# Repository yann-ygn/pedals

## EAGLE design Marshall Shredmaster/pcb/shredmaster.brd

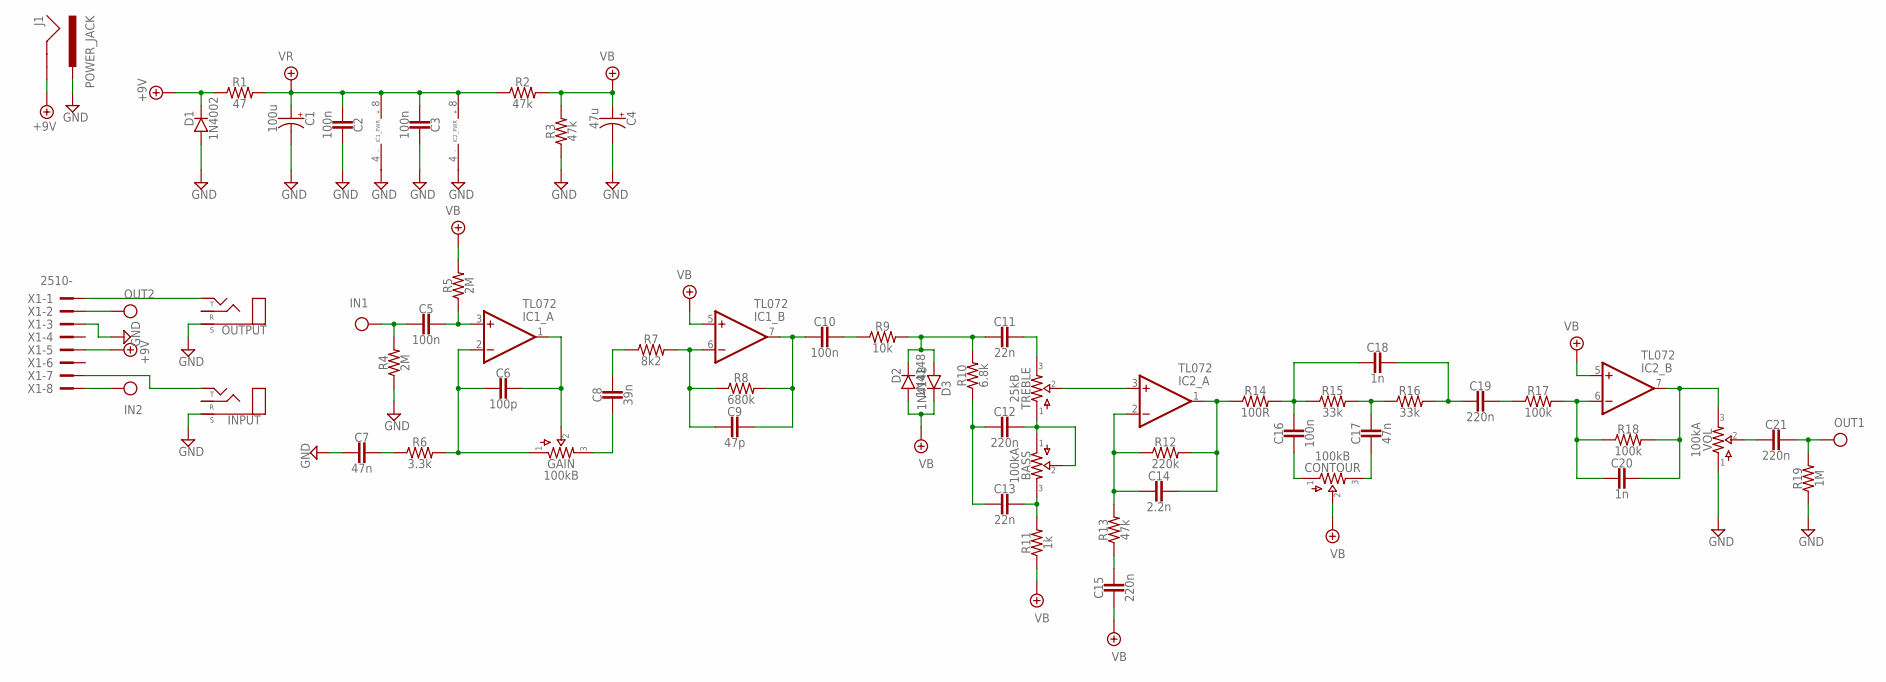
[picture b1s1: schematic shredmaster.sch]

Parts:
BASS: 100kA; 16MM
C1: 100u; 040_020
C2, C3: 100n; 050X030_025_2
C4: 47u; 040_020
C5, C10, C16: 100n; BOX_SMALL
C6: 100p; 050X030_025_2
C7, C17: 47n; BOX_SMALL
C8: 39n; BOX_SMALL
C9: 47p; 050X030_025_2
C11, C13: 22n; BOX_SMALL
C12, C15, C19, C21: 220n; BOX_SMALL
C14: 2.2n; BOX_SMALL
C18, C20: 1n; BOX_SMALL
CONTOUR: 100kB; 16MM
D1: 1N4002; DO41-2
D2, D3: 1N4148; DO35-2
GAIN: 100kB; 16MM
IC1, IC2: TL072; DIL08
INPUT: STEREONMJ; NMJ6HCD2
J1: POWER_JACK; POWER_JACK_PTH
OUTPUT: STEREONMJ; NMJ6HCD2
R1: 47; R0207/3
R2, R3, R13: 47k; R0207/3
R4, R5: 2M; R0207/3
R6: 3.3k; R0207/3
R7: 8k2; R0207/3
R8: 680k; R0207/3
R9: 10k; R0207/3
R10: 6.8k; R0207/3
R11: 1k; R0207/3
R12: 220k; R0207/3
R14: 100R; R0207/3
R15, R16: 33k; R0207/3
R17, R18: 100k; R0207/3
R19: 1M; R0207/3
TREBLE: 25kB; 16MM
VOL: 100kA; 16MM
X1: 2510-; PAK100/2500-10

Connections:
+9V: D1.C, J1.GND, R1.1, X1.5
GND: C1.-, C2.1, C3.1, C4.-, C7.2, D1.A, IC1.4 (V-), IC2.4 (V-), INPUT.S, J1.PWR, OUTPUT.S, R3.1, R4.1, R19.1, VOL.1, X1.3
IN: C5.2, R4.2, X1.8
unnamed: INPUT.T, X1.7
unnamed: C5.1, IC1.3 (+IN), R5.1
unnamed: C6.1, GAIN.2, IC1.1 (OUT)
unnamed: OUTPUT.T, X1.1
unnamed: C6.2, GAIN.1, IC1.2 (-IN), R6.2
unnamed: C7.1, R6.1
unnamed: C8.2, GAIN.3
unnamed: C8.1, R7.1
unnamed: C9.2, IC1.6 (-IN), R7.2, R8.1
unnamed: C9.1, C10.2, IC1.7 (OUT), R8.2
unnamed: C10.1, R9.1
unnamed: C11.2, D2.C, D3.A, R9.2, R10.2
unnamed: C11.1, TREBLE.3
unnamed: C12.2, C13.2, R10.1
unnamed: BASS.1, BASS.2, C12.1, TREBLE.1
unnamed: BASS.3, C13.1, R11.2
unnamed: C21.2, VOL.2
unnamed: C14.2, IC2.2 (-IN), R12.1, R13.2
unnamed: C14.1, IC2.1 (OUT), R12.2, R14.1
unnamed: IC2.3 (+IN), TREBLE.2
unnamed: C15.1, R13.1
unnamed: C16.2, CONTOUR.1
unnamed: C17.2, CONTOUR.3
unnamed: C16.1, C18.2, R14.2, R15.1
unnamed: C17.1, R15.2, R16.1
unnamed: C18.1, C19.2, R16.2
unnamed: C19.1, R17.1
unnamed: C20.2, IC2.6 (-IN), R17.2, R18.1
unnamed: C20.1, IC2.7 (OUT), R18.2, VOL.3
OUT: C21.1, R19.2, X1.2
VB: C4.+, C15.2, CONTOUR.2, D2.A, D3.C, IC1.5 (+IN), IC2.5 (+IN), R2.2, R3.2, R5.2, R11.1
VR: C1.+, C2.2, C3.2, IC1.8 (V+), IC2.8 (V+), R1.2, R2.1

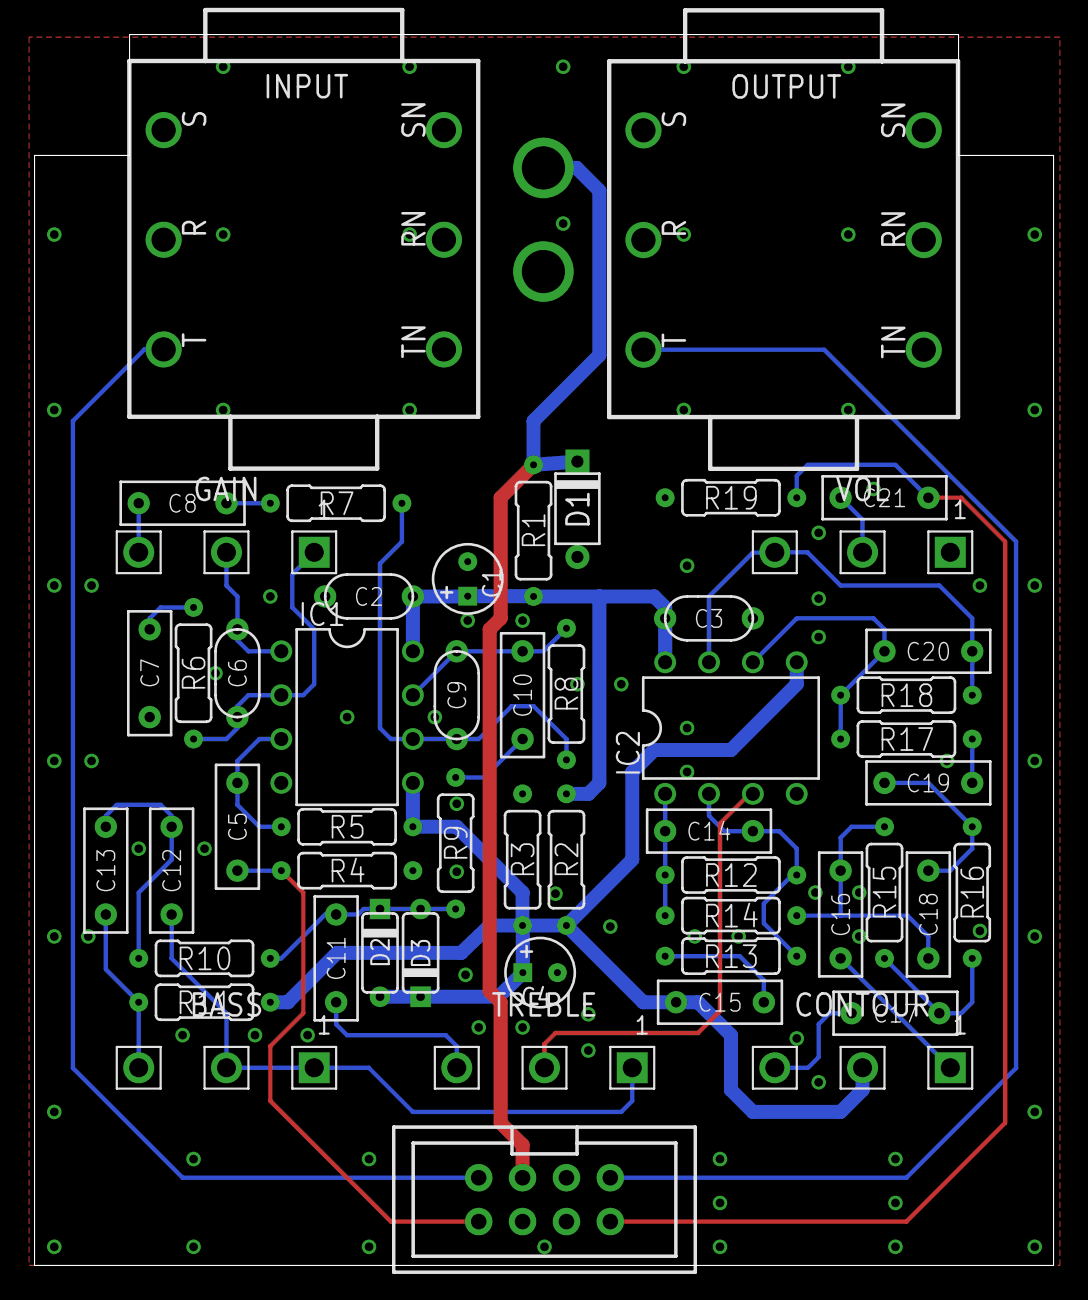
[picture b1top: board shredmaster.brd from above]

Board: 2 copper layers, 59.0 x 71.3 mm, 55 parts (1 on the bottom side), 35 nets.

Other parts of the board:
U$1: 125B_PCB

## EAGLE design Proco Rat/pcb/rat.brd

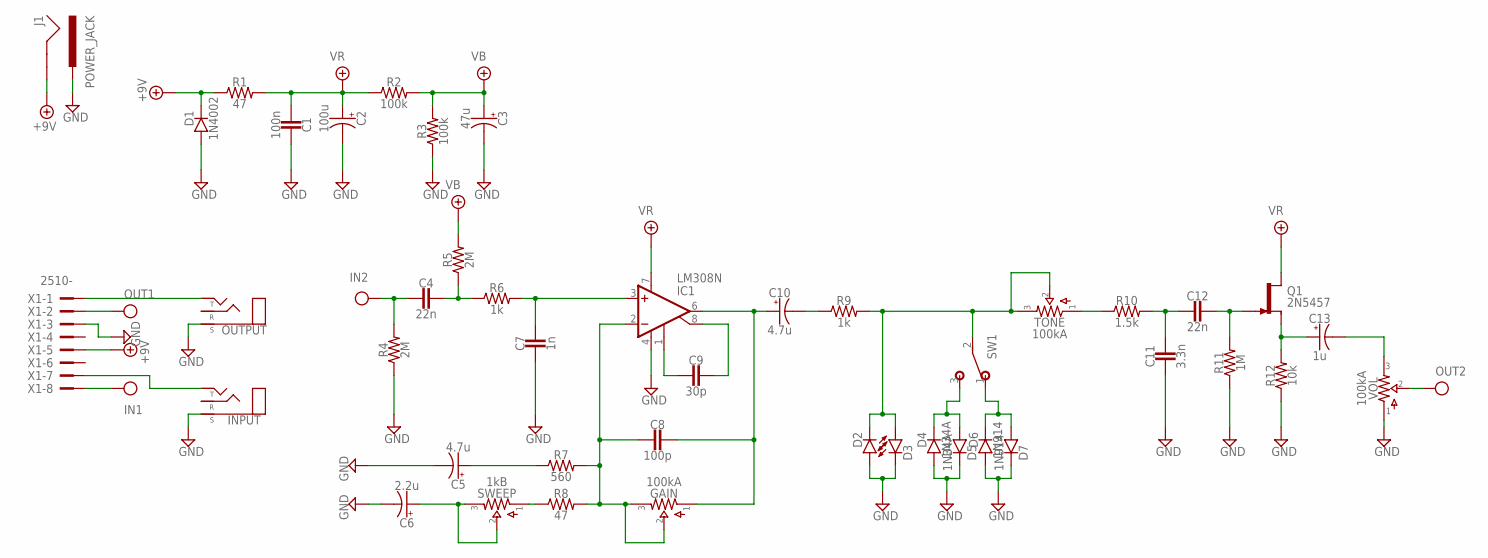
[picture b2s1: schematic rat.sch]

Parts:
C1: 100n; 050X030_025_2
C2: 100u; 040_020
C3: 47u; 040_020
C4, C12: 22n; BOX_SMALL
C5, C10: 4.7u; 050_020
C6: 2.2u; 050_020
C7: 1n; BOX_SMALL
C8: 100p; 050X030_025_2
C9: 30p; 050X030_025_2
C11: 3.3n; BOX_SMALL
C13: 1u; 050_020
D1: 1N4002; DO41-2
D2, D3: LED; 3MM_D
D4, D5: 1N34A; DO35-2
D6, D7: 1N914; DO35-2
GAIN: 100kA; 16MM
IC1: LM308N; DIL08
INPUT: STEREONMJ; NMJ6HCD2
J1: POWER_JACK; POWER_JACK_PTH
OUTPUT: STEREONMJ; NMJ6HCD2
Q1: 2N5457; TO92-
R1, R8: 47; R0207/3
R2, R3: 100k; R0207/3
R4, R5: 2M; R0207/3
R6, R9: 1k; R0207/3
R7: 560; R0207/3
R10: 1.5k; R0207/3
R11: 1M; R0207/3
R12: 10k; R0207/3
SW1: SPDT; M9040P
SWEEP: 1kB; 16MM
TONE: 100kA; 16MM
VOL: 100kA; 16MM
X1: 2510-; PAK100/2500-10

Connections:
+9V: D1.C, J1.GND, R1.1, X1.5
GND: C1.1, C2.-, C3.-, C5.-, C6.-, C7.2, C11.2, D1.A, D2.ANODE (A), D3.P$1 (C), D4.A, D5.C, D6.A, D7.C, IC1.4 (V-), INPUT.S, J1.PWR, OUTPUT.S, R3.1, R4.1, R11.1, R12.1, VOL.1, X1.3
IN: C4.2, R4.2, X1.8
unnamed: INPUT.T, X1.7
unnamed: C4.1, R5.1, R6.1
unnamed: C7.1, IC1.3 (+IN), R6.2
unnamed: OUTPUT.T, X1.1
unnamed: R8.1, SWEEP.1
unnamed: C9.2, IC1.1 (CMP1)
unnamed: C9.1, IC1.8 (CMP2)
unnamed: C8.1, C10.+, GAIN.1, IC1.6 (OUT)
unnamed: C5.+, R7.1
unnamed: C6.+, SWEEP.2, SWEEP.3
unnamed: C10.-, R9.1
unnamed: D2.P$1 (C), D3.ANODE (A), R9.2, SW1.2, TONE.2, TONE.3
unnamed: C8.2, GAIN.2, GAIN.3, IC1.2 (-IN), R7.2, R8.2
unnamed: R10.1, TONE.1
unnamed: C11.1, C12.2, R10.2
unnamed: C12.1, Q1.1 (G), R11.2
unnamed: C13.+, Q1.2 (S), R12.2
unnamed: C13.-, VOL.3
unnamed: D4.C, D5.A, SW1.3 (S)
unnamed: D6.C, D7.A, SW1.1 (O)
OUT: VOL.2, X1.2
VB: C3.+, R2.2, R3.2, R5.2
VR: C1.2, C2.+, IC1.7 (V+), Q1.3 (D), R1.2, R2.1

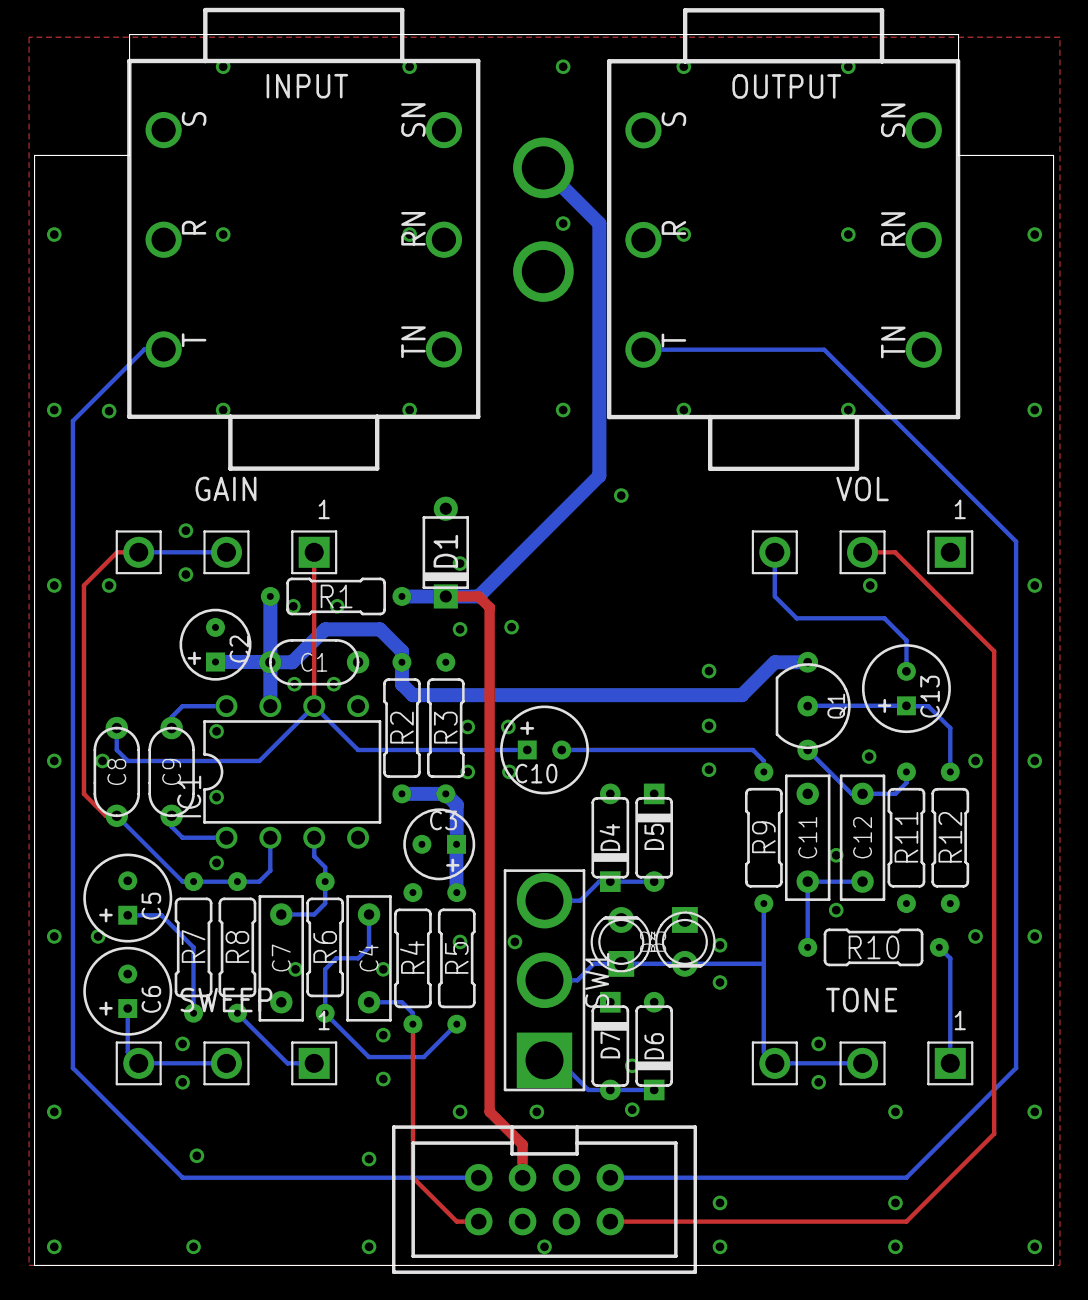
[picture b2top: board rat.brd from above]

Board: 2 copper layers, 59.0 x 71.3 mm, 44 parts (1 on the bottom side), 26 nets.

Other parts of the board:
U$1: 125B_PCB

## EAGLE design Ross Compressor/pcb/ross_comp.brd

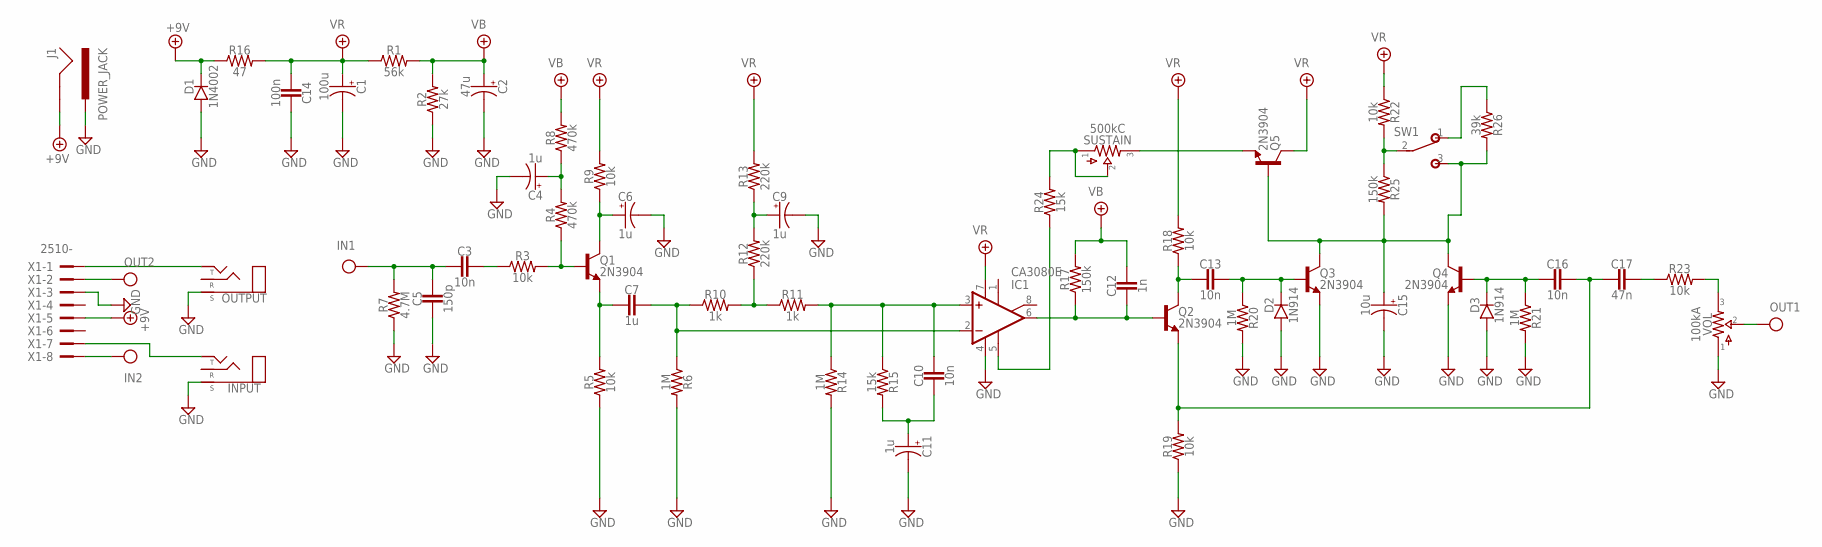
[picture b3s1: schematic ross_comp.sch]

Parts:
C1: 100u; 040_020
C2: 47u; 040_020
C3, C10, C13, C16: 10n; BOX_SMALL
C4, C6, C9, C11: 1u; 040_020
C5: 150p; 050X030_025_2
C7: 1u; BOX_BIG
C12: 1n; BOX_SMALL
C14: 100n; BOX_SMALL
C15: 10u; 040_020
C17: 47n; BOX_SMALL
D1: 1N4002; DO41-2
D2, D3: 1N914; DO35-2
IC1: CA3080E; DIL08
INPUT: STEREONMJ; NMJ6HCD2
J1: POWER_JACK; POWER_JACK_PTH
OUTPUT: STEREONMJ; NMJ6HCD2
Q1, Q2, Q3, Q4, Q5: 2N3904; TO92-
R1: 56k; R0207/3
R2: 27k; R0207/3
R3, R5, R9, R18, R19, R22, R23: 10k; R0207/3
R4, R8: 470k; R0207/3
R6, R14, R20, R21: 1M; R0207/3
R7: 4.7M; R0207/3
R10, R11: 1k; R0207/3
R12, R13: 220k; R0207/3
R15, R24: 15k; R0207/3
R16: 47; R0207/3
R17, R25: 150k; R0207/3
R26: 39k; R0207/3
SUSTAIN: 500kC; 16MM
SW1: SPDT; M9040P
VOL: 100kA; 16MM
X1: 2510-; PAK100/2500-10

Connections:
+9V: D1.C, J1.GND, R16.1, X1.5
GND: C1.-, C2.-, C4.-, C5.2, C6.-, C9.-, C11.-, C14.1, C15.-, D1.A, D2.A, D3.A, IC1.4 (V-), INPUT.S, J1.PWR, OUTPUT.S, Q3.3 (E), Q4.3 (E), R2.1, R5.1, R6.2, R7.1, R14.2, R19.1, R20.2, R21.2, VOL.1, X1.3
IN: C3.2, C5.1, R7.2, X1.8
unnamed: INPUT.T, X1.7
unnamed: C3.1, R3.1
unnamed: Q1.2 (B), R3.2, R4.1
unnamed: OUTPUT.T, X1.1
unnamed: C4.+, R4.2, R8.1
unnamed: R26.1, SW1.1 (O)
unnamed: C6.+, Q1.1 (C), R9.1
unnamed: C7.1, IC1.2 (-IN), R6.1, R10.1
unnamed: C7.2, Q1.3 (E), R5.2
unnamed: C10.1, IC1.3 (+IN), R11.2, R14.1, R15.1
unnamed: R10.2, R11.1, R12.1
unnamed: C9.+, R12.2, R13.1
unnamed: C10.2, C11.+, R15.2
unnamed: C13.2, Q2.1 (C), R18.1
unnamed: C12.2, IC1.6 (OUT), Q2.2 (B), R17.1
unnamed: C16.1, C17.2, Q2.3 (E), R19.2
unnamed: C13.1, D2.C, Q3.2 (B), R20.1
unnamed: C15.+, Q3.1 (C), Q4.1 (C), Q5.2 (B), R25.2, R26.2, SW1.3 (S)
unnamed: C16.2, D3.C, Q4.2 (B), R21.1
unnamed: R22.2, R25.1, SW1.2
unnamed: C17.1, R23.1
unnamed: R23.2, VOL.3
unnamed: Q5.3 (E), SUSTAIN.3
unnamed: R24.2, SUSTAIN.1, SUSTAIN.2
unnamed: IC1.5 (OPT), R24.1
OUT: VOL.2, X1.2
VB: C2.+, C12.1, R1.2, R2.2, R8.2, R17.2
VR: C1.+, C14.2, IC1.7 (V+), Q5.1 (C), R1.1, R9.2, R13.2, R16.2, R18.2, R22.1

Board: 2 copper layers, 59 parts (1 on the bottom side), 31 nets, no tracks yet.

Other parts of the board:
U$1: 125B_PCB

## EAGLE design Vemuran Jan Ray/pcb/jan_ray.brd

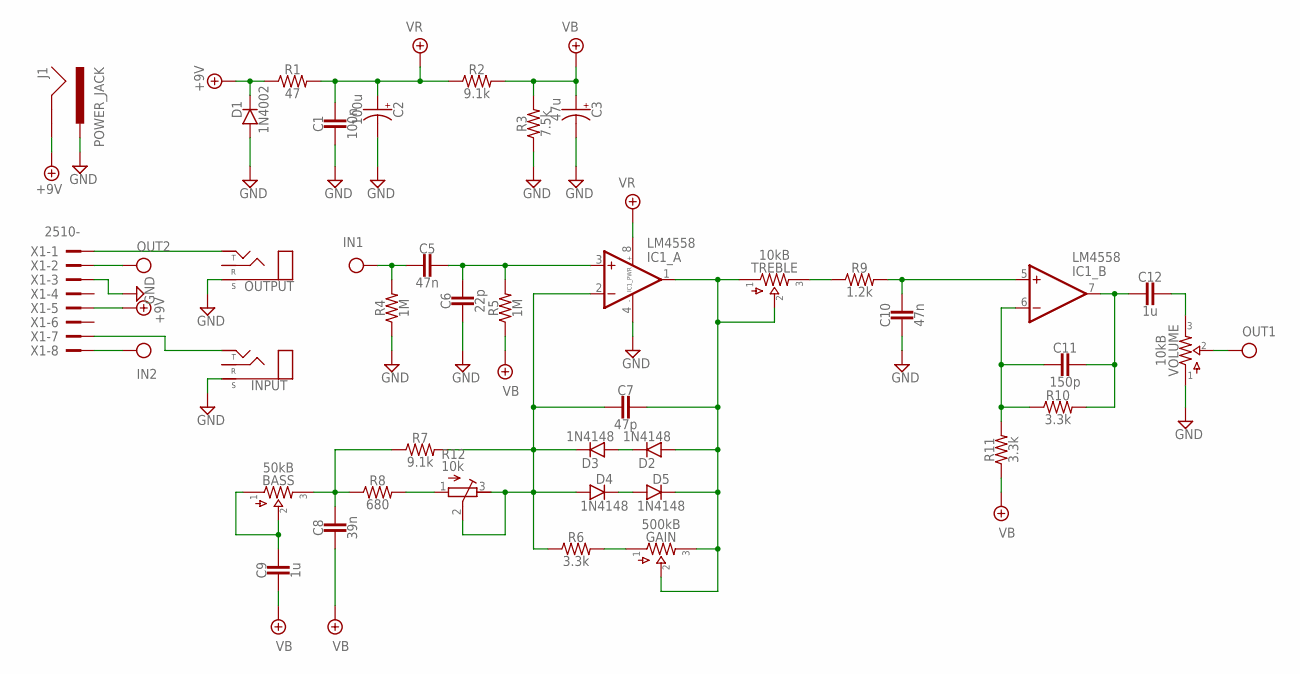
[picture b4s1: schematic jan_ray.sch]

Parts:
BASS: 50kB; 16MM
C1: 100n; 050X030_025_2
C2: 100u; 050_020
C3: 47u; 050_020
C5, C10: 47n; BOX_SMALL
C6: 22p; 050X030_025_2
C7: 47p; 050X030_025_2
C8: 39n; BOX_SMALL
C9, C12: 1u; BOX_BIG
C11: 150p; 050X030_025_2
D1: 1N4002; DO41-2
D2, D3, D4, D5: 1N4148; DO35-2
GAIN: 500kB; 16MM
IC1: LM4558; DIL08
INPUT: STEREONMJ; NMJ6HCD2
J1: POWER_JACK; POWER_JACK_PTH
OUTPUT: STEREONMJ; NMJ6HCD2
R1: 47; R0207/3
R2, R7: 9.1k; R0207/3
R3: 7.5k; R0207/3
R4, R5: 1M; R0207/3
R6, R10, R11: 3.3k; R0207/3
R8: 680; R0207/3
R9: 1.2k; R0207/3
R12: 10k; RTRIM3296W
TREBLE: 10kB; 16MM
VOLUME: 10kB; 16MM
X1: 2510-; PAK100/2500-10

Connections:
+9V: D1.C, J1.GND, R1.1, X1.5
GND: C1.2, C2.-, C3.-, C6.2, C10.2, D1.A, IC1.4 (V-), INPUT.S, J1.PWR, OUTPUT.S, R3.1, R4.1, VOLUME.1, X1.3
IN: C5.2, R4.2, X1.8
unnamed: INPUT.T, X1.7
unnamed: C5.1, C6.1, IC1.3 (+IN), R5.2
unnamed: OUTPUT.T, X1.1
unnamed: C7.2, D3.C, D4.A, IC1.2 (-IN), R6.1, R7.2, R12.2 (S), R12.3 (E)
unnamed: C7.1, D2.A, D5.C, GAIN.2, GAIN.3, IC1.1 (OUT), TREBLE.1, TREBLE.2
unnamed: GAIN.1, R6.2
unnamed: D2.C, D3.A
unnamed: D4.C, D5.A
unnamed: R8.2, R12.1 (A)
unnamed: BASS.3, C8.1, R7.1, R8.1
unnamed: R9.1, TREBLE.3
unnamed: BASS.1, BASS.2, C9.1
unnamed: C10.1, IC1.5 (+IN), R9.2
unnamed: C11.2, IC1.6 (-IN), R10.1, R11.2
unnamed: C11.1, C12.2, IC1.7 (OUT), R10.2
unnamed: C12.1, VOLUME.3
OUT: VOLUME.2, X1.2
VB: C3.+, C8.2, C9.2, R2.2, R3.2, R5.1, R11.1
VR: C1.1, C2.+, IC1.8 (V+), R1.2, R2.1

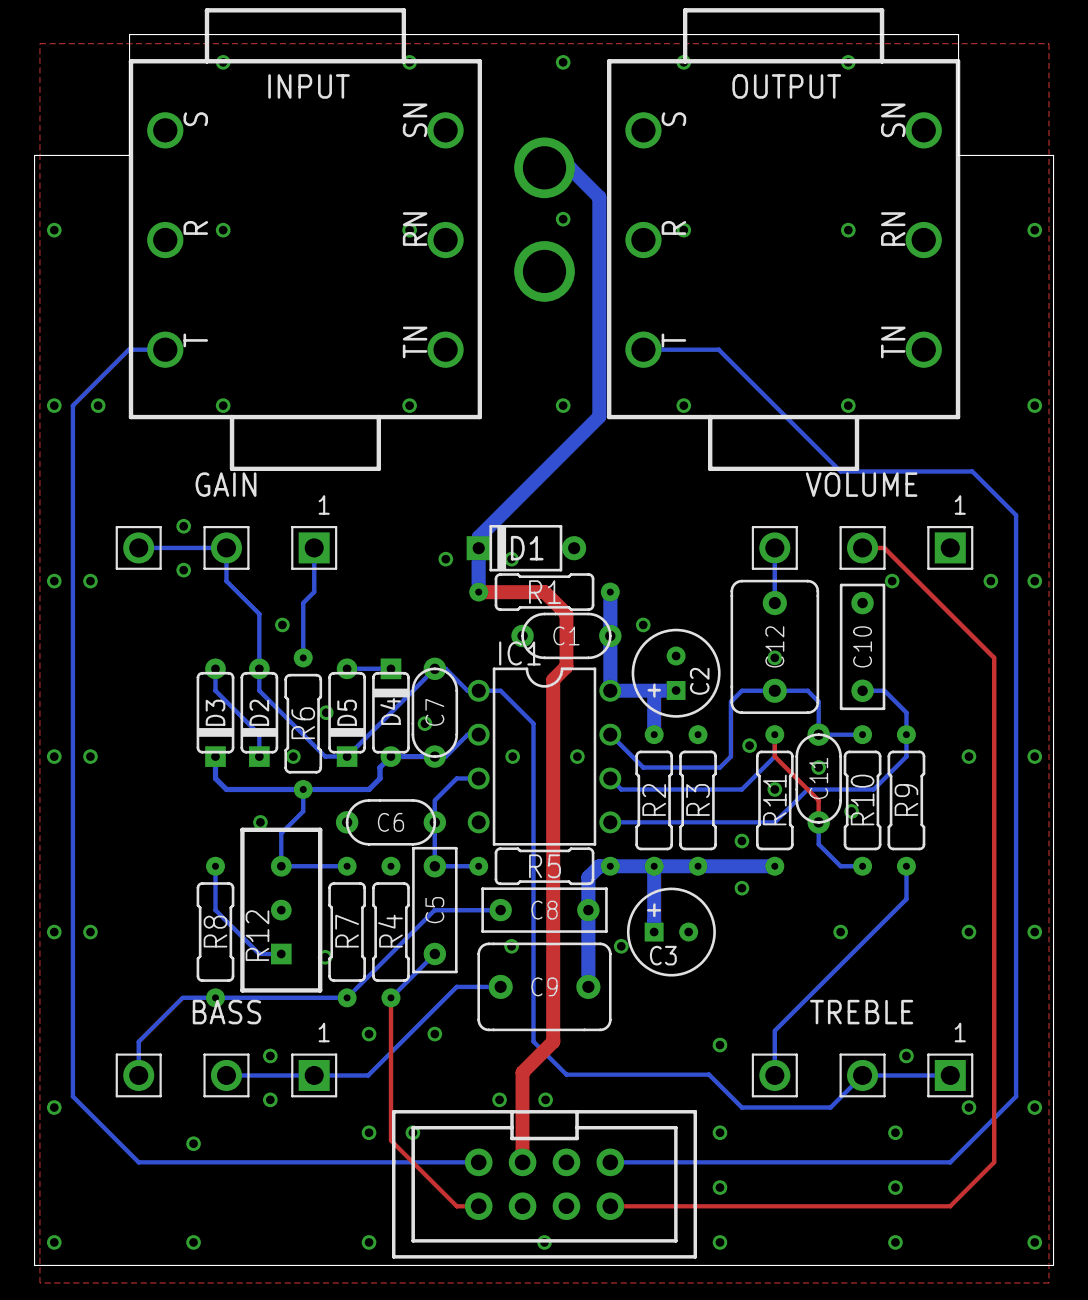
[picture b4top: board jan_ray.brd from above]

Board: 2 copper layers, 59.0 x 71.3 mm, 38 parts (1 on the bottom side), 22 nets.

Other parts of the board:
U$1: 125B_PCB
